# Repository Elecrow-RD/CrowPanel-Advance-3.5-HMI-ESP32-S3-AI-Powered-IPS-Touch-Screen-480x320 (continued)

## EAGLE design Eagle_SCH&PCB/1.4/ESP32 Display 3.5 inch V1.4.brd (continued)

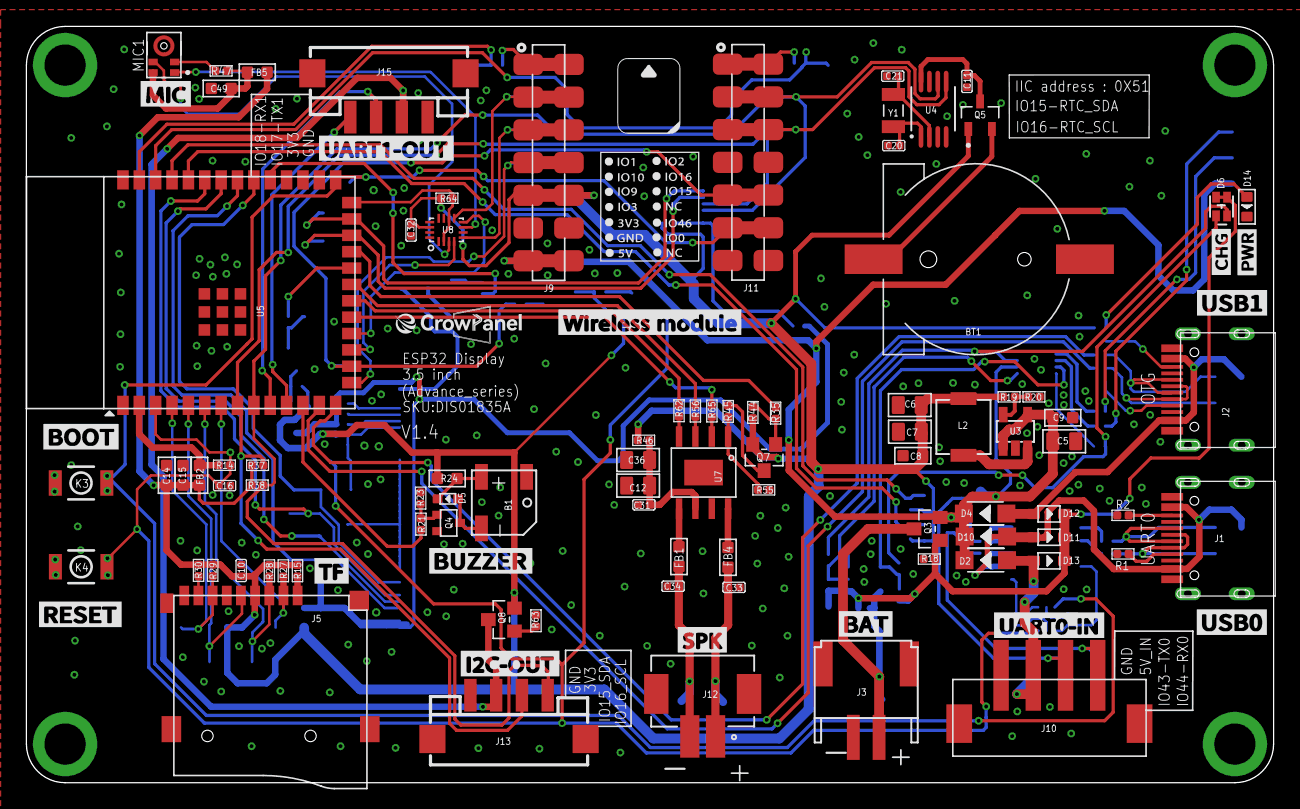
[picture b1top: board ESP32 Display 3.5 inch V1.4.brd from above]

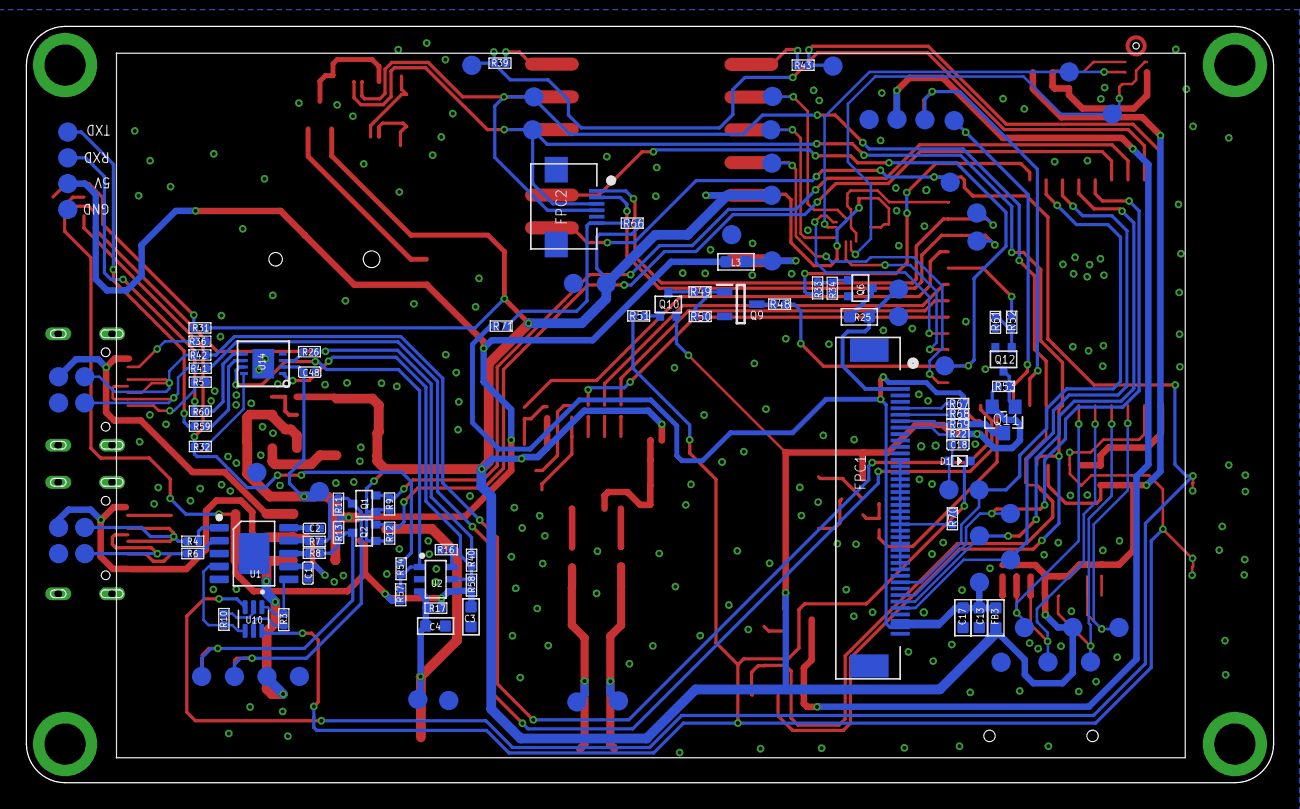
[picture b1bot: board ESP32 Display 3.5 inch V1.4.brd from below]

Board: 2 copper layers, 96.8 x 58.7 mm, 213 parts (123 on the bottom side), 123 nets.

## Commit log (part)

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2025-10-31 Fix formatting in version table in readme.md
2026-04-24 sync example
2026-06-04 libraries
2026-06-04 ESP32S3-120M
2026-06-24 update project files
2026-06-24 Thread
2026-06-24 ESP_IDF
